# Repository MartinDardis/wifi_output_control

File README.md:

# Control de salidas - ESP8266 WiFi

## Caracteristicas Generales:

* Modo Station o Access Point automatico
* Soporte ARDUINO OTA y WEB OTA (update con firm.bin)
* Configuracion red WiFi y Login almacenada en memoria flash.
* Soporta hasta 2 salidas en simultaneo (PCB para 1 o 2).

## Diagrama de Cableado

Los pines **1,2,3** pertenecen al relay 1, donde 2 (NEGRO) es la entrada, 1 (AMARILLO) es la salida normal cerrada y 3 (ROJO) la normal abierta.

Los pines **4,5,6** pertenecen al relay 2, donde 5 (NEGRO) es la entrada, 4 (AMARILLO) es la salida normal cerrada y 6 (ROJO) la normal abierta.

Los pines de **VCC** (AZUL) y **GND** (NEGRO), pueden recibir entre 5 y 20 V. No deben ser utilizados si se alimenta el modulo mediante el puerto USB.

## Primer Uso

Una vez realizado el cableado se procede a la configuracion inicial.

1.  Una vez conectado, alimentar el circuito y esperar que el LED azul quede encendido fijo.
2.	Ya en modo AP, conectarse a la red del tip ESPXXX (XXX representa los ultimos numeros MAC del dispositivo).
3.	Mediante el navegador, ingresar a la pagina de control. http://192.168.4.1
4.	Ir a la pestaña Configuracion y ingresar los datos de la red que se quiere utilizar.
5. 	Reiniciar dispositivo. EL led comenzara a titilar, en caso de que pasado un tiempo no pueda conectarse volvera a encenderse fijo. Repetir la Configuracion. Si queda apagado la conexion tuvo exito.

Nota: El dispositivo admite conexion Serial USB, **Baudrate: 115200**

### TO DO

* Añadir mas salidas (Rediseño de PCB).
* Almacenar mas de un ssid a la vez.
* SPIFFS OTA
* Terminar el readme

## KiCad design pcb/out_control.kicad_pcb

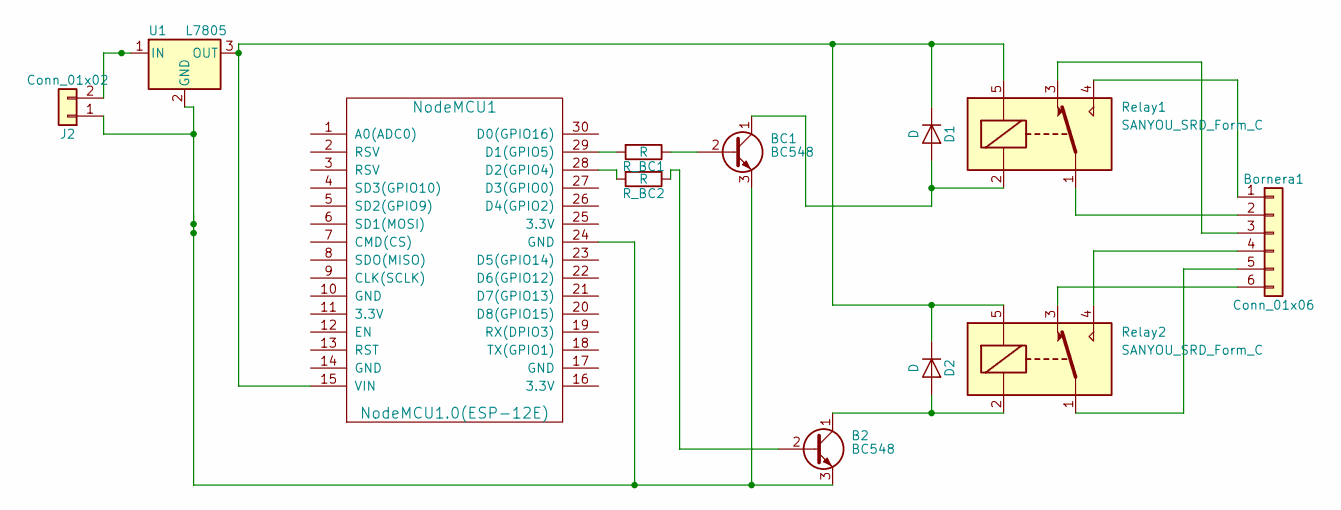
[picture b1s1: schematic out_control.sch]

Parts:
B2: BC548; TO-92_Molded_Wide
BC1: BC548; TO-92_Molded_Wide
Bornera1: Conn_01x06; TerminalBlock_4UCON_19963_06x3.5mm_Straight
D1, D2: D; D_T-1_P10.16mm_Horizontal
J2: Conn_01x02; TerminalBlock_4UCON_19963_02x3.5mm_Straight
NodeMCU1: NodeMCU1.0(ESP-12E); NodeMCU_Amica_R2
R_BC1, R_BC2: R; R_Axial_DIN0411_L9.9mm_D3.6mm_P12.70mm_Horizontal
Relay1, Relay2: SANYOU_SRD_Form_C; Relay_SPDT_SANYOU_SRD_Series_Form_C
U1: L7805; TO-220

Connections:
unnamed: B2.1 (C), D2.2 (A), Relay2.2
unnamed: B2.2 (B), R_BC2.1
unnamed: B2.3 (E), BC1.3 (E), J2.1, NodeMCU1.24 (GND), U1.2 (GND)
unnamed: BC1.1 (C), D1.2 (A), Relay1.2
unnamed: BC1.2 (B), R_BC1.1
unnamed: Bornera1.1, Relay1.4
unnamed: Bornera1.2, Relay1.1
unnamed: Bornera1.3, Relay1.3
unnamed: Bornera1.4, Relay2.4
unnamed: Bornera1.5, Relay2.1
unnamed: Bornera1.6, Relay2.3
unnamed: D1.1 (K), D2.1 (K), NodeMCU1.15 (VIN), Relay1.5, Relay2.5, U1.3 (OUT)
unnamed: J2.2, U1.1 (IN)
unnamed: NodeMCU1.28 (D2(GPIO4)), R_BC2.2
unnamed: NodeMCU1.29 (D1(GPIO5)), R_BC1.2

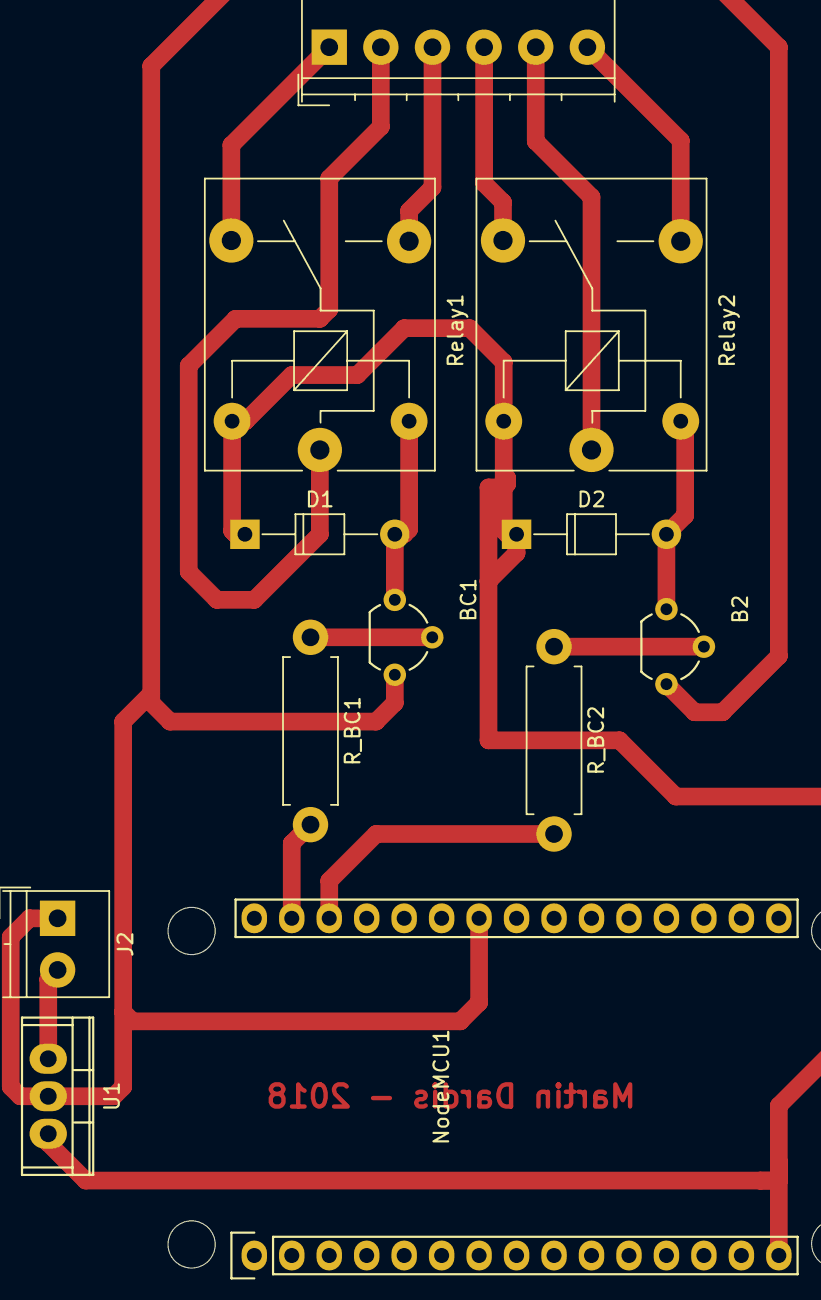
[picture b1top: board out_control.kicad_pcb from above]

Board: 2 copper layers, 12 parts (0 on the bottom side), 15 nets.

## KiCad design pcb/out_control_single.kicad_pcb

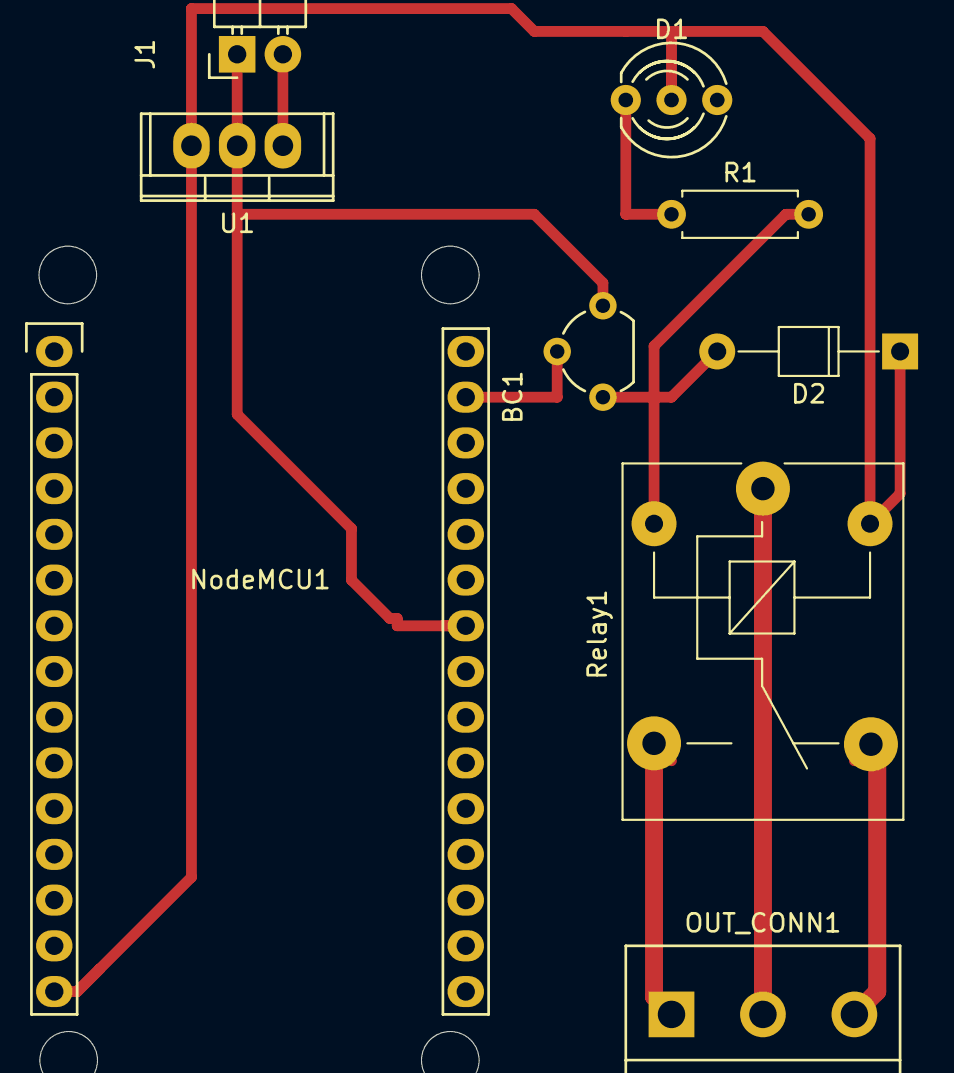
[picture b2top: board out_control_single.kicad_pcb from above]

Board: 2 copper layers, 9 parts (0 on the bottom side), 9 nets.

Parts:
BC1: BC548; TO-92_Molded_Wide
D1: LED; LED-5MM-3
D2: D; D_T-1_P10.16mm_Horizontal
J1: Conn_01x02; Pin_Header_Angled_1x02
NodeMCU1: NodeMCU1.0(ESP-12E); NodeMCU_Amica_R2
OUT_CONN1: Conn_01x03; bornier3
R1: R; R_Axial_DIN0207_L6.3mm_D2.5mm_P7.62mm_Horizontal
Relay1: SANYOU_SRD_Form_C; Relay_SPDT_SANYOU_SRD_Series_Form_C
U1: L7805; TO-220

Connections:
unnamed: BC1.1, D2.2, R1.2, Relay1.2
unnamed: BC1.2, NodeMCU1.29
unnamed: BC1.3, J1.1, NodeMCU1.24, U1.2
unnamed: D1.1, R1.1
unnamed: D1.2, D2.1, NodeMCU1.15, Relay1.5, U1.3
unnamed: J1.2, U1.1
unnamed: OUT_CONN1.1, Relay1.3
unnamed: OUT_CONN1.2, Relay1.1
unnamed: OUT_CONN1.3, Relay1.4

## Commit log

2018-08-17 First commit - README Update
2018-08-18 Improves security - Add login [WEB]
2018-08-18 Improves security - Add login [SERVER]
2018-08-18 Update TODO
2018-08-19 [FIX] security bug who can manage output without login - [WIP] change user-pass
2018-08-19 [NEW][FRONT] add user-pass page
2018-08-20 [NEW] User - pass NOW can be changed
2018-08-20 config parameter moved to a header file
2018-08-20 add error page
2018-08-20 [NEW] Update from web are now available
2018-08-20 [FIX] restart module after factory reset
2018-08-21 [README] update
2018-08-21 [RELEASE] bin V1.0
2018-08-23 [FIX] No wifi config dont wait to AP mode - More connecting time
2018-08-23 [RELEASE] v.1.1 - Minor fix and no wait for AP mode
2018-08-27 [FIX] after reset now recover outputs status info
2018-08-27 [RELEASE] firmware V1.3
2018-09-03 [FIX] bug overwrite MAC ADDRESS with WEB_OTA_PASS, now values is allocated in heap
2018-09-03 [FIX] bug overwrite MAC ADDRESS with WEB_OTA_PASS, now values is allocated in heap - [NEW] /erase now reset password (dev use)
2018-10-23 [NEW_UI] login redesign
2018-10-23 [NEW_UI] login form names fixed
2019-12-13 some fixes
2019-12-16 refactor v1.1
2019-12-16 remove files in refactor
2019-12-18 refactor FS
2019-12-18 add bootstrap
2019-12-18 V1.4
2019-12-21 MD: change rest response to JSON
2019-12-26 Add ionic mobile app
2019-12-26 security fix
2019-12-27 Some bugs - some fixes
2019-12-27 fix CORS
2020-04-05 Bump acorn from 6.4.0 to 6.4.1 in /mobile
    Bumps [acorn](https://github.com/acornjs/acorn) from 6.4.0 to 6.4.1.
    - [Release notes](https://github.com/acornjs/acorn/releases)
    - [Commits](https://github.com/acornjs/acorn/compare/6.4.0...6.4.1)
2020-06-07 Bump websocket-extensions from 0.1.3 to 0.1.4 in /mobile
    Bumps [websocket-extensions](https://github.com/faye/websocket-extensions-node) from 0.1.3 to 0.1.4.
    - [Release notes](https://github.com/faye/websocket-extensions-node/releases)
    - [Changelog](https://github.com/faye/websocket-extensions-node/blob/master/CHANGELOG.md)
    - [Commits](https://github.com/faye/websocket-extensions-node/compare/0.1.3...0.1.4)
2020-07-19 Bump lodash from 4.17.15 to 4.17.19 in /mobile
    Bumps [lodash](https://github.com/lodash/lodash) from 4.17.15 to 4.17.19.
    - [Release notes](https://github.com/lodash/lodash/releases)
    - [Commits](https://github.com/lodash/lodash/compare/4.17.15...4.17.19)
2020-08-01 Bump elliptic from 6.5.2 to 6.5.3 in /mobile
    Bumps [elliptic](https://github.com/indutny/elliptic) from 6.5.2 to 6.5.3.
    - [Release notes](https://github.com/indutny/elliptic/releases)
    - [Commits](https://github.com/indutny/elliptic/compare/v6.5.2...v6.5.3)
2020-09-11 Bump http-proxy from 1.18.0 to 1.18.1 in /mobile
    Bumps [http-proxy](https://github.com/http-party/node-http-proxy) from 1.18.0 to 1.18.1.
    - [Release notes](https://github.com/http-party/node-http-proxy/releases)
    - [Changelog](https://github.com/http-party/node-http-proxy/blob/master/CHANGELOG.md)
    - [Commits](https://github.com/http-party/node-http-proxy/compare/1.18.0...1.18.1)
2021-03-10 Bump elliptic from 6.5.2 to 6.5.4 in /mobile
    Bumps [elliptic](https://github.com/indutny/elliptic) from 6.5.2 to 6.5.4.
    - [Release notes](https://github.com/indutny/elliptic/releases)
    - [Commits](https://github.com/indutny/elliptic/compare/v6.5.2...v6.5.4)
2021-03-31 Bump y18n from 4.0.0 to 4.0.1 in /mobile
    Bumps [y18n](https://github.com/yargs/y18n) from 4.0.0 to 4.0.1.
    - [Release notes](https://github.com/yargs/y18n/releases)
    - [Changelog](https://github.com/yargs/y18n/blob/master/CHANGELOG.md)
    - [Commits](https://github.com/yargs/y18n/commits)
2021-04-30 Bump ssri from 6.0.1 to 6.0.2 in /mobile
    Bumps [ssri](https://github.com/npm/ssri) from 6.0.1 to 6.0.2.
    - [Release notes](https://github.com/npm/ssri/releases)
    - [Changelog](https://github.com/npm/ssri/blob/v6.0.2/CHANGELOG.md)
    - [Commits](https://github.com/npm/ssri/compare/v6.0.1...v6.0.2)
2021-05-07 Bump underscore from 1.9.1 to 1.13.1 in /mobile
    Bumps [underscore](https://github.com/jashkenas/underscore) from 1.9.1 to 1.13.1.
    - [Release notes](https://github.com/jashkenas/underscore/releases)
    - [Commits](https://github.com/jashkenas/underscore/compare/1.9.1...1.13.1)
2021-05-08 Bump handlebars from 4.5.3 to 4.7.7 in /mobile
    Bumps [handlebars](https://github.com/wycats/handlebars.js) from 4.5.3 to 4.7.7.
    - [Release notes](https://github.com/wycats/handlebars.js/releases)
    - [Changelog](https://github.com/handlebars-lang/handlebars.js/blob/master/release-notes.md)
    - [Commits](https://github.com/wycats/handlebars.js/compare/v4.5.3...v4.7.7)
2021-05-09 Bump url-parse from 1.4.7 to 1.5.1 in /mobile
    Bumps [url-parse](https://github.com/unshiftio/url-parse) from 1.4.7 to 1.5.1.
    - [Release notes](https://github.com/unshiftio/url-parse/releases)
    - [Commits](https://github.com/unshiftio/url-parse/compare/1.4.7...1.5.1)
2021-05-10 Bump lodash from 4.17.15 to 4.17.21 in /mobile
    Bumps [lodash](https://github.com/lodash/lodash) from 4.17.15 to 4.17.21.
    - [Release notes](https://github.com/lodash/lodash/releases)
    - [Commits](https://github.com/lodash/lodash/compare/4.17.15...4.17.21)
2021-05-11 Bump hosted-git-info from 2.8.5 to 2.8.9 in /mobile
    Bumps [hosted-git-info](https://github.com/npm/hosted-git-info) from 2.8.5 to 2.8.9.
    - [Release notes](https://github.com/npm/hosted-git-info/releases)
    - [Changelog](https://github.com/npm/hosted-git-info/blob/v2.8.9/CHANGELOG.md)
    - [Commits](https://github.com/npm/hosted-git-info/compare/v2.8.5...v2.8.9)
2021-05-28 Bump dns-packet from 1.3.1 to 1.3.4 in /mobile
    Bumps [dns-packet](https://github.com/mafintosh/dns-packet) from 1.3.1 to 1.3.4.
    - [Release notes](https://github.com/mafintosh/dns-packet/releases)
    - [Changelog](https://github.com/mafintosh/dns-packet/blob/master/CHANGELOG.md)
    - [Commits](https://github.com/mafintosh/dns-packet/compare/v1.3.1...v1.3.4)
